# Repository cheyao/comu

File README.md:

# Comu

A bite-sized CH32V203 board that fits inside your USB port.

Intrested? Get one on [Crowd Supply](https://www.crowdsupply.com/icy-electronics/comu)!

Comu is a tiny CH32V203 RISC-V computer that fits inside a USB port. It is user programmable, fitted with a custom bootloader, has four captive touch buttons and two LEDs. The board is supported by [ch32fun](https://github.com/cnlohr/ch32fun), allowing easy and lightweight RISC-V bare-metal development.

The CH32V203 is equipped with 248KB of Flash and 20KB of SRAM, more than enough for most embedded applications. The chip also has a wide array of peripherals, including DMA and a 12bit ADC, allowing for a wide variety of uses. The board also exposes 6 GPIO pins via testpoints, allowing it to be embedded on custom boards for further use.

It can also easily act as a **USB HID device**, allowing portable key injections to avoid repetitive typing. With it 4 captive buttons, you can make it into a sliding volume adjuster, computer sleep trigger, screen capture device and more!

### No bloat, no weight

Using bare-metal programming in C/C++, the RISC-V program created for this chip contains 0 bloat. The minimal size of a blinky is only **40 bytes**, compared to 324KB on Arduino Pico or 12KB with Pico SDK. The [CH32V203 RM](https://www.wch-ic.com/downloads/CH32FV2x_V3xRM_PDF.html) contains all information needed to use the MCU, from register descriptions to memory layout.

The board is also very lightweight, weighing merely **0.4g** (0.2g without case). Measuring a mere 13x9.4mm, it occupies nearly no space.

Even in such constrained space, the board still boasts rich peripherals. You can directly access 2 white LEDs and 4 captive buttons. The captive buttons are double-sided edge-plated, ensuring accurate touch sensing. It is also easy to use thanks to the CH32V203's touchkey peripheral, directly handling all the troublesome parts of touch sensing. (Example in `examples/touch` folder).

### USB explorer

The CH32V203 is perfect for USB packet exploring. Its bare and well-documented USBD peripheral allows you to manipulate raw packets, while taking care of troublesome parts such as transaction handling. You can directly pair this with [usbmon](https://docs.kernel.org/usb/usbmon.html) on Wireshark to explore how USB transactions work.

### Custom bootloader

The board comes pre-programmed with a sleek custom USB bootloader to compensate for the lack of a BOOT0 button and the large size of the official bootloader. The custom bootloader is only **2KiB** in size, freeing up the 28KiB of boot flash for user use.

The bootloader is also completely open source; check out its source code in the `bootloader` folder. The only quirk is that the programs must be linked to `0x800` and flashed to 0x800, but that is taken care by the provided Makefile in the examples folder.

### Bare metal isn't your thing?

No worries! The CH32V203 is also supported by a wide array of tools: Rust via [ch32-hal](https://github.com/ch32-rs/ch32-hal), Arduino via [arduino_core_ch32](https://github.com/openwch/arduino_core_ch32), or normal WCH-HAL via [Mounriver Studio II](https://mounriver.com/download).

USB communication can be completely handled by libraries such as [tinyusb](https://docs.tinyusb.org/en/latest/index.html) or [ch32fun's usbd lib](https://github.com/cnlohr/ch32fun/blob/master/extralibs/usbd.c). All raw peripherals can also be hidden by Mounriver's HAL.

### Tons of examples

There are tons of examples in the `examples` folder on this repo, and also compatible with the examples in [ch32fun](https://github.com/cnlohr/ch32fun).

### Features

- [CH32V203](https://wch-ic.com/products/CH32V203.html) 32bit RISC-V MCU
    - 224KB Flash, 24KB Boot Flash, 20KB SRAM (64KB 0-wait Flash and 160KB Normal Flash)
    - 144MHz with internal oscillator
    - 12bit ADC
    - 49.3 μA/MHz @ run and 19.4 μA/MHz @ sleep
    - USB full speed peripheral
- 4x Captive touch buttons w/ castellated edges
- 2x LEDs
- 6x GPIOs broken out via testpads
- Fits in a USB-A connector

### Pins

- LED1: PB11
- LED2: PA4
- Captive touch:
    - A5 (PA5)
    - A7 (PA7)
    - A8 (PB0)
    - A9 (PB1)
- GPIOs: PB14, PB15, PA1, PA2, PA3, PA8

### Usage

Dependencies: Make, riscv64-gcc, libusb (Checkout dependency list [here](https://github.com/cnlohr/ch32fun/wiki/Installation))

Clone this respository and pull the submodules:

```
$ git clone https://github.com/cheyao/comu
$ cd comu
$ git submodule update --init --recursive
```

Go into the examples folder and build an example:

```
$ cd examples/blink
$ make
```

Now, the example should be built. When you insert your Comu into your USB port, it should stay in the bootloader for the first 5 seconds. You can then re-run `make flash` to flash the binary onto the chip!

Now you can make your applications! I recommend starting off by copying an example, as you need to flash to address `flash+0x800` to avoid overwriting the custom bootloader.

If the flashing isn't working, please read through this [wiki](https://github.com/cnlohr/ch32fun/wiki/Installation) for operating system setup, and try re-building minichnlink. (I've submitted a few new patches for the ch32v203 flashing a week ago)

### Can I get one?

They will be shortly availiable on [Crowd Supply](https://www.crowdsupply.com/icy-electronics/comu)!

### Attributions

Form factor credit goes to tomu.

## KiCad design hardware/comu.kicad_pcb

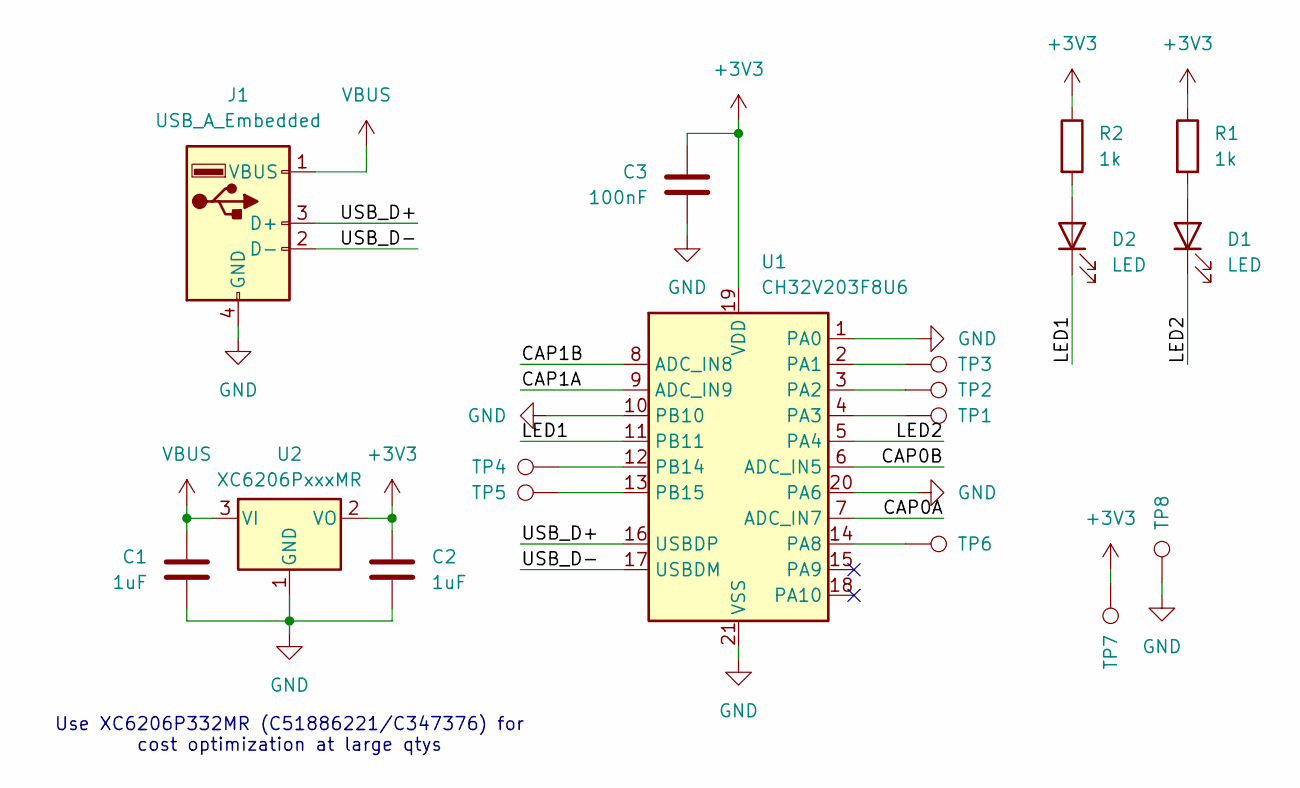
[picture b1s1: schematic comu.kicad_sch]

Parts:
C1, C2: 1uF; C_0402_1005Metric; LCSC Part # C52923
C3: 100nF; C_0402_1005Metric; LCSC Part # C1525
D1, D2: LED; LED_0402_1005Metric; LCSC Part # C22355736
J1: USB_A_Embedded; USB_A_Connector_PCB
R1, R2: 1k; R_0402_1005Metric; LCSC Part # C11702
TP1, TP2, TP3, TP4, TP5, TP6, TP7, TP8: TestPoint; TestPoint_Pad_D0.6mm
U1: CH32V203F8U6; QFN-20-1EP_3x3mm_P0.4mm_EP1.65x1.65mm; LCSC Part # C7570477
U2: XC6206PxxxMR; SOT-23-3; LCSC Part # C51886221

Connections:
+3V3: C2.1, C3.1, R1.1, R2.1, TP7.1 (1_1), U1.19 (VDD), U2.2 (VO)
/CAP0A: U1.7 (ADC_IN7)
/CAP0B: U1.6 (ADC_IN5)
/CAP1A: U1.9 (ADC_IN9)
/CAP1B: U1.8 (ADC_IN8)
/LED1: D2.1 (K), U1.11 (PB11)
/LED2: D1.1 (K), U1.5 (PA4)
/USB_D+: J1.3 (D+), U1.16 (USBDP)
/USB_D-: J1.2 (D-), U1.17 (USBDM)
GND: C1.2, C2.2, C3.2, J1.4 (GND), TP8.1 (1_1), U1.1 (PA0), U1.10 (PB10), U1.20 (PA6), U1.21 (VSS), U2.1 (GND)
unnamed: D1.2 (A), R1.2
unnamed: D2.2 (A), R2.2
unnamed: TP3.1 (1_1), U1.2 (PA1)
unnamed: TP2.1 (1_1), U1.3 (PA2)
unnamed: TP1.1 (1_1), U1.4 (PA3)
unnamed: TP6.1 (1_1), U1.14 (PA8)
unnamed: TP4.1 (1_1), U1.12 (PB14)
unnamed: TP5.1 (1_1), U1.13 (PB15)
VBUS: C1.1, J1.1 (VBUS), U2.3 (VI)

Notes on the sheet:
Use XC6206P332MR (C51886221/C347376) for cost optimization at large qtys

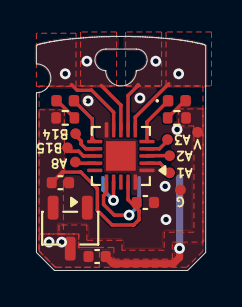
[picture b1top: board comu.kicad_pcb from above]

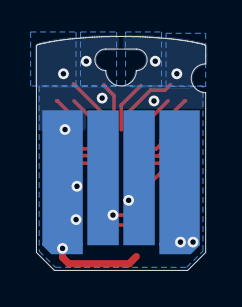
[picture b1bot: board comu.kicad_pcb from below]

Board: 2 copper layers, 9.4 x 13.0 mm, 19 parts (2 on the bottom side), 15 nets.

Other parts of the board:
XX1: Button solder mask removal; soldermask-removal

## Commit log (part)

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2026-03-31 Init
2026-05-08 Change USB pad type to edge-connector

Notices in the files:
hardware/comu.kicad_pcb:
License: Solderpad
